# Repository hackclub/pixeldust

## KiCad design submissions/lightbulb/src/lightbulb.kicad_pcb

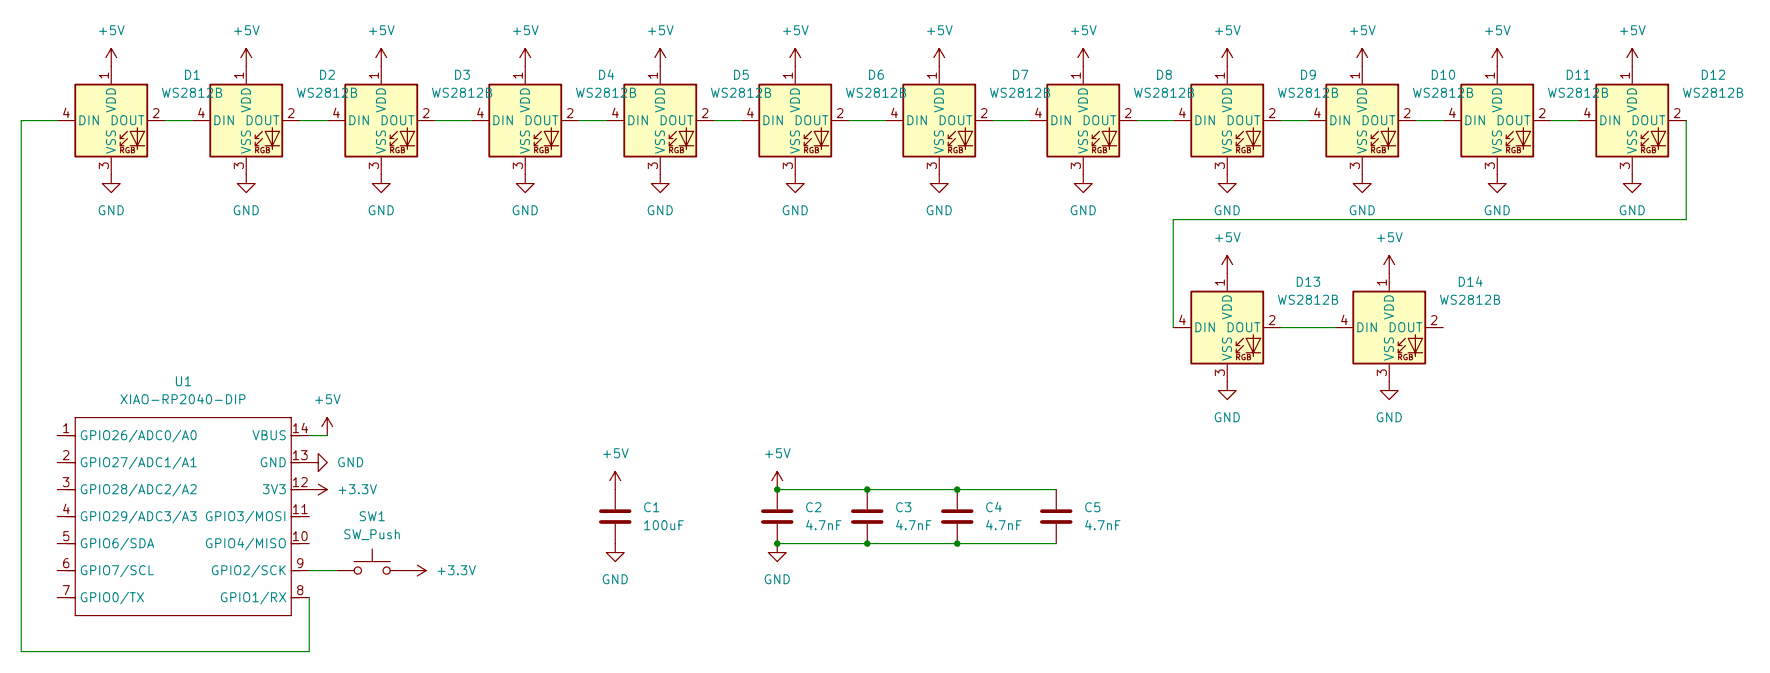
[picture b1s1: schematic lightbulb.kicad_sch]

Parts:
C1: 100uF; C_1206_3216Metric_Pad1.33x1.80mm_HandSolder
C2, C3, C4, C5: 4.7nF; C_0402_1005Metric_Pad0.74x0.62mm_HandSolder
D1, D2, D3, D4, D5, D6, D7, D8, D9, D10, D11, D12, D13, D14: WS2812B; LED_WS2812B_PLCC4_5.0x5.0mm_P3.2mm
SW1: SW_Push; SW_Cherry_MX_1.00u_PCB
U1: XIAO-RP2040-DIP

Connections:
+3.3V: SW1.2, U1.12 (3V3)
+5V: C1.1, C2.1, C3.1, C4.1, C5.1, D1.1 (VDD), D2.1 (VDD), D3.1 (VDD), D4.1 (VDD), D5.1 (VDD), D6.1 (VDD), D7.1 (VDD), D8.1 (VDD), D9.1 (VDD), D10.1 (VDD), D11.1 (VDD), D12.1 (VDD), D13.1 (VDD), D14.1 (VDD), U1.14 (VBUS)
GND: C1.2, C2.2, C3.2, C4.2, C5.2, D1.3 (VSS), D2.3 (VSS), D3.3 (VSS), D4.3 (VSS), D5.3 (VSS), D6.3 (VSS), D7.3 (VSS), D8.3 (VSS), D9.3 (VSS), D10.3 (VSS), D11.3 (VSS), D12.3 (VSS), D13.3 (VSS), D14.3 (VSS), U1.13 (GND)
unnamed: D1.4 (DIN), U1.8 (GPIO1/RX)
unnamed: D1.2 (DOUT), D2.4 (DIN)
unnamed: D2.2 (DOUT), D3.4 (DIN)
unnamed: D3.2 (DOUT), D4.4 (DIN)
unnamed: D4.2 (DOUT), D5.4 (DIN)
unnamed: D5.2 (DOUT), D6.4 (DIN)
unnamed: D6.2 (DOUT), D7.4 (DIN)
unnamed: D7.2 (DOUT), D8.4 (DIN)
unnamed: D8.2 (DOUT), D9.4 (DIN)
unnamed: D9.2 (DOUT), D10.4 (DIN)
unnamed: D10.2 (DOUT), D11.4 (DIN)
unnamed: D11.2 (DOUT), D12.4 (DIN)
unnamed: D12.2 (DOUT), D13.4 (DIN)
unnamed: D13.2 (DOUT), D14.4 (DIN)
unnamed: SW1.1, U1.9 (GPIO2/SCK)

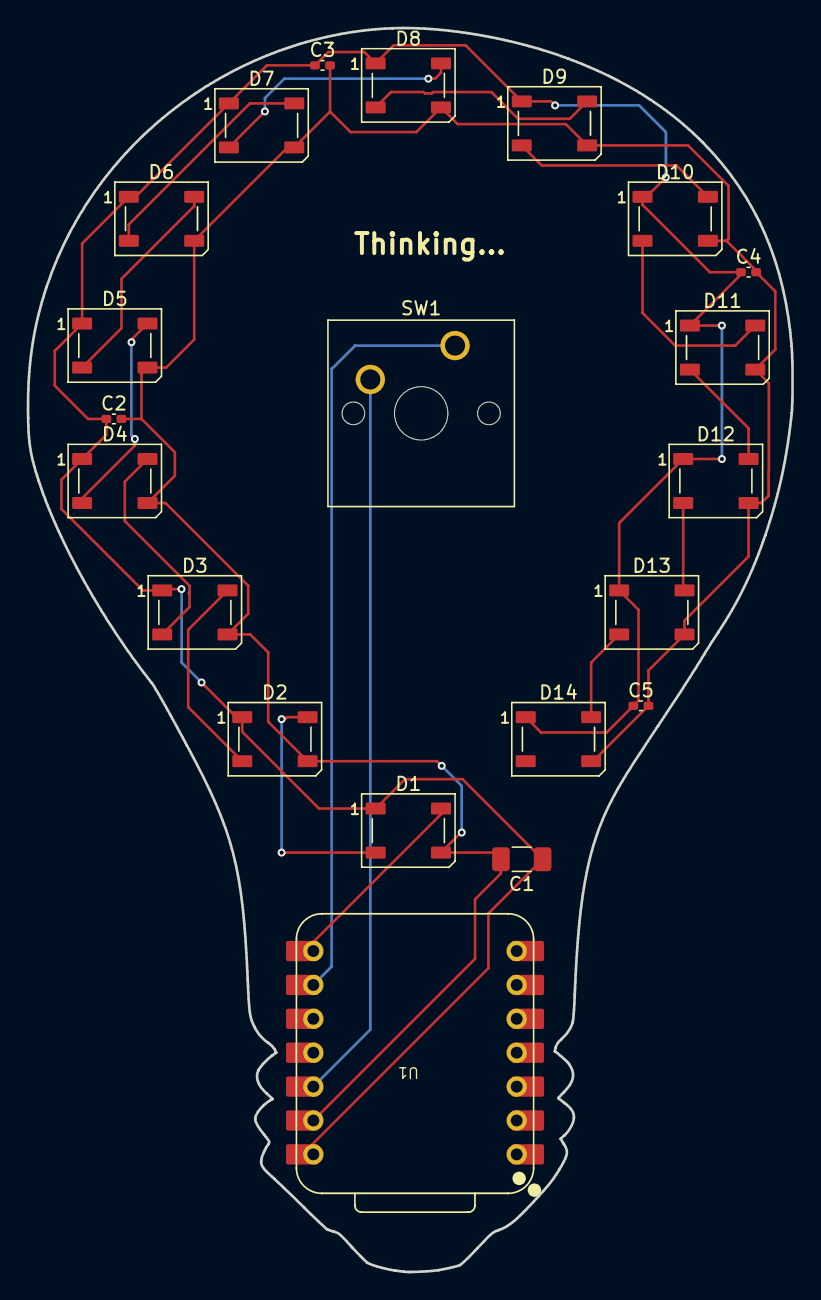
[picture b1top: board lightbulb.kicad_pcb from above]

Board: 2 copper layers, 57.3 x 93.2 mm, 21 parts (0 on the bottom side), 18 nets.

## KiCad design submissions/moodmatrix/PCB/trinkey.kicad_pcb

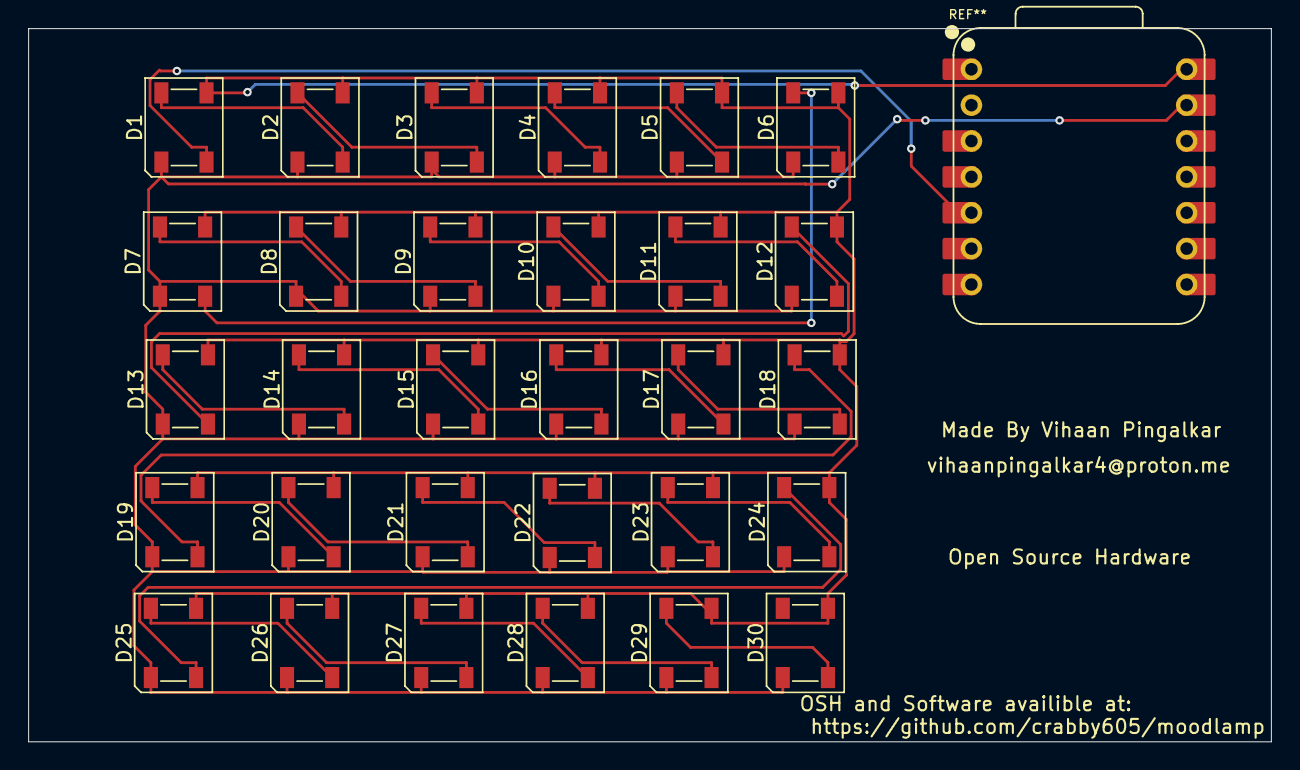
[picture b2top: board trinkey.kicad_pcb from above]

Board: 2 copper layers, 88.0 x 50.5 mm, 30 parts (0 on the bottom side), 31 nets.

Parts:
D1, D2, D3, D4, D5, D6, D7, D8, D9, D10, D11, D12, D13, D14, D15, D16, D17, D18, D19, D20, D21, D22, D23, D24, D25, D26, D27, D28, D29, D30: SK6812; LED_SK6812_PLCC4_5.0x5.0mm_P3.2mm

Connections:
+5V: D1.3 (VDD), D2.3 (VDD), D3.3 (VDD), D4.3 (VDD), D5.3 (VDD), D6.3 (VDD), D7.3 (VDD), D8.3 (VDD), D9.3 (VDD), D10.3 (VDD), D11.3 (VDD), D12.3 (VDD), D13.3 (VDD), D14.3 (VDD), D15.3 (VDD), D16.3 (VDD), D17.3 (VDD), D18.3 (VDD), D19.3 (VDD), D20.3 (VDD), D21.3 (VDD), D22.3 (VDD), D23.3 (VDD), D24.3 (VDD), D25.3 (VDD), D26.3 (VDD), D27.3 (VDD), D28.3 (VDD), D29.3 (VDD), D30.3 (VDD)
GND: D1.1 (VSS), D2.1 (VSS), D3.1 (VSS), D4.1 (VSS), D5.1 (VSS), D6.1 (VSS), D7.1 (VSS), D8.1 (VSS), D9.1 (VSS), D10.1 (VSS), D11.1 (VSS), D12.1 (VSS), D13.1 (VSS), D14.1 (VSS), D15.1 (VSS), D16.1 (VSS), D17.1 (VSS), D18.1 (VSS), D19.1 (VSS), D20.1 (VSS), D21.1 (VSS), D22.1 (VSS), D23.1 (VSS), D24.1 (VSS), D25.1 (VSS), D26.1 (VSS), D27.1 (VSS), D28.1 (VSS), D29.1 (VSS), D30.1 (VSS)
unnamed: D1.4 (DOUT), D2.2 (DIN)
unnamed: D2.4 (DOUT), D3.2 (DIN)
unnamed: D3.4 (DOUT), D4.2 (DIN)
unnamed: D4.4 (DOUT), D5.2 (DIN)
unnamed: D5.4 (DOUT), D6.2 (DIN)
unnamed: D6.4 (DOUT), D7.2 (DIN)
unnamed: D7.4 (DOUT), D8.2 (DIN)
unnamed: D8.4 (DOUT), D9.2 (DIN)
unnamed: D9.4 (DOUT), D10.2 (DIN)
unnamed: D10.4 (DOUT), D11.2 (DIN)
unnamed: D11.4 (DOUT), D12.2 (DIN)
unnamed: D12.4 (DOUT), D13.2 (DIN)
unnamed: D13.4 (DOUT), D14.2 (DIN)
unnamed: D14.4 (DOUT), D15.2 (DIN)
unnamed: D15.4 (DOUT), D16.2 (DIN)
unnamed: D16.4 (DOUT), D17.2 (DIN)
unnamed: D17.4 (DOUT), D18.2 (DIN)
unnamed: D18.4 (DOUT), D19.2 (DIN)
unnamed: D19.4 (DOUT), D20.2 (DIN)
unnamed: D20.4 (DOUT), D21.2 (DIN)
unnamed: D21.4 (DOUT), D22.2 (DIN)
unnamed: D22.4 (DOUT), D23.2 (DIN)
unnamed: D23.4 (DOUT), D24.2 (DIN)
unnamed: D24.4 (DOUT), D25.2 (DIN)
unnamed: D25.4 (DOUT), D26.2 (DIN)
unnamed: D26.4 (DOUT), D27.2 (DIN)
unnamed: D27.4 (DOUT), D28.2 (DIN)
unnamed: D28.4 (DOUT), D29.2 (DIN)
unnamed: D29.4 (DOUT), D30.2 (DIN)

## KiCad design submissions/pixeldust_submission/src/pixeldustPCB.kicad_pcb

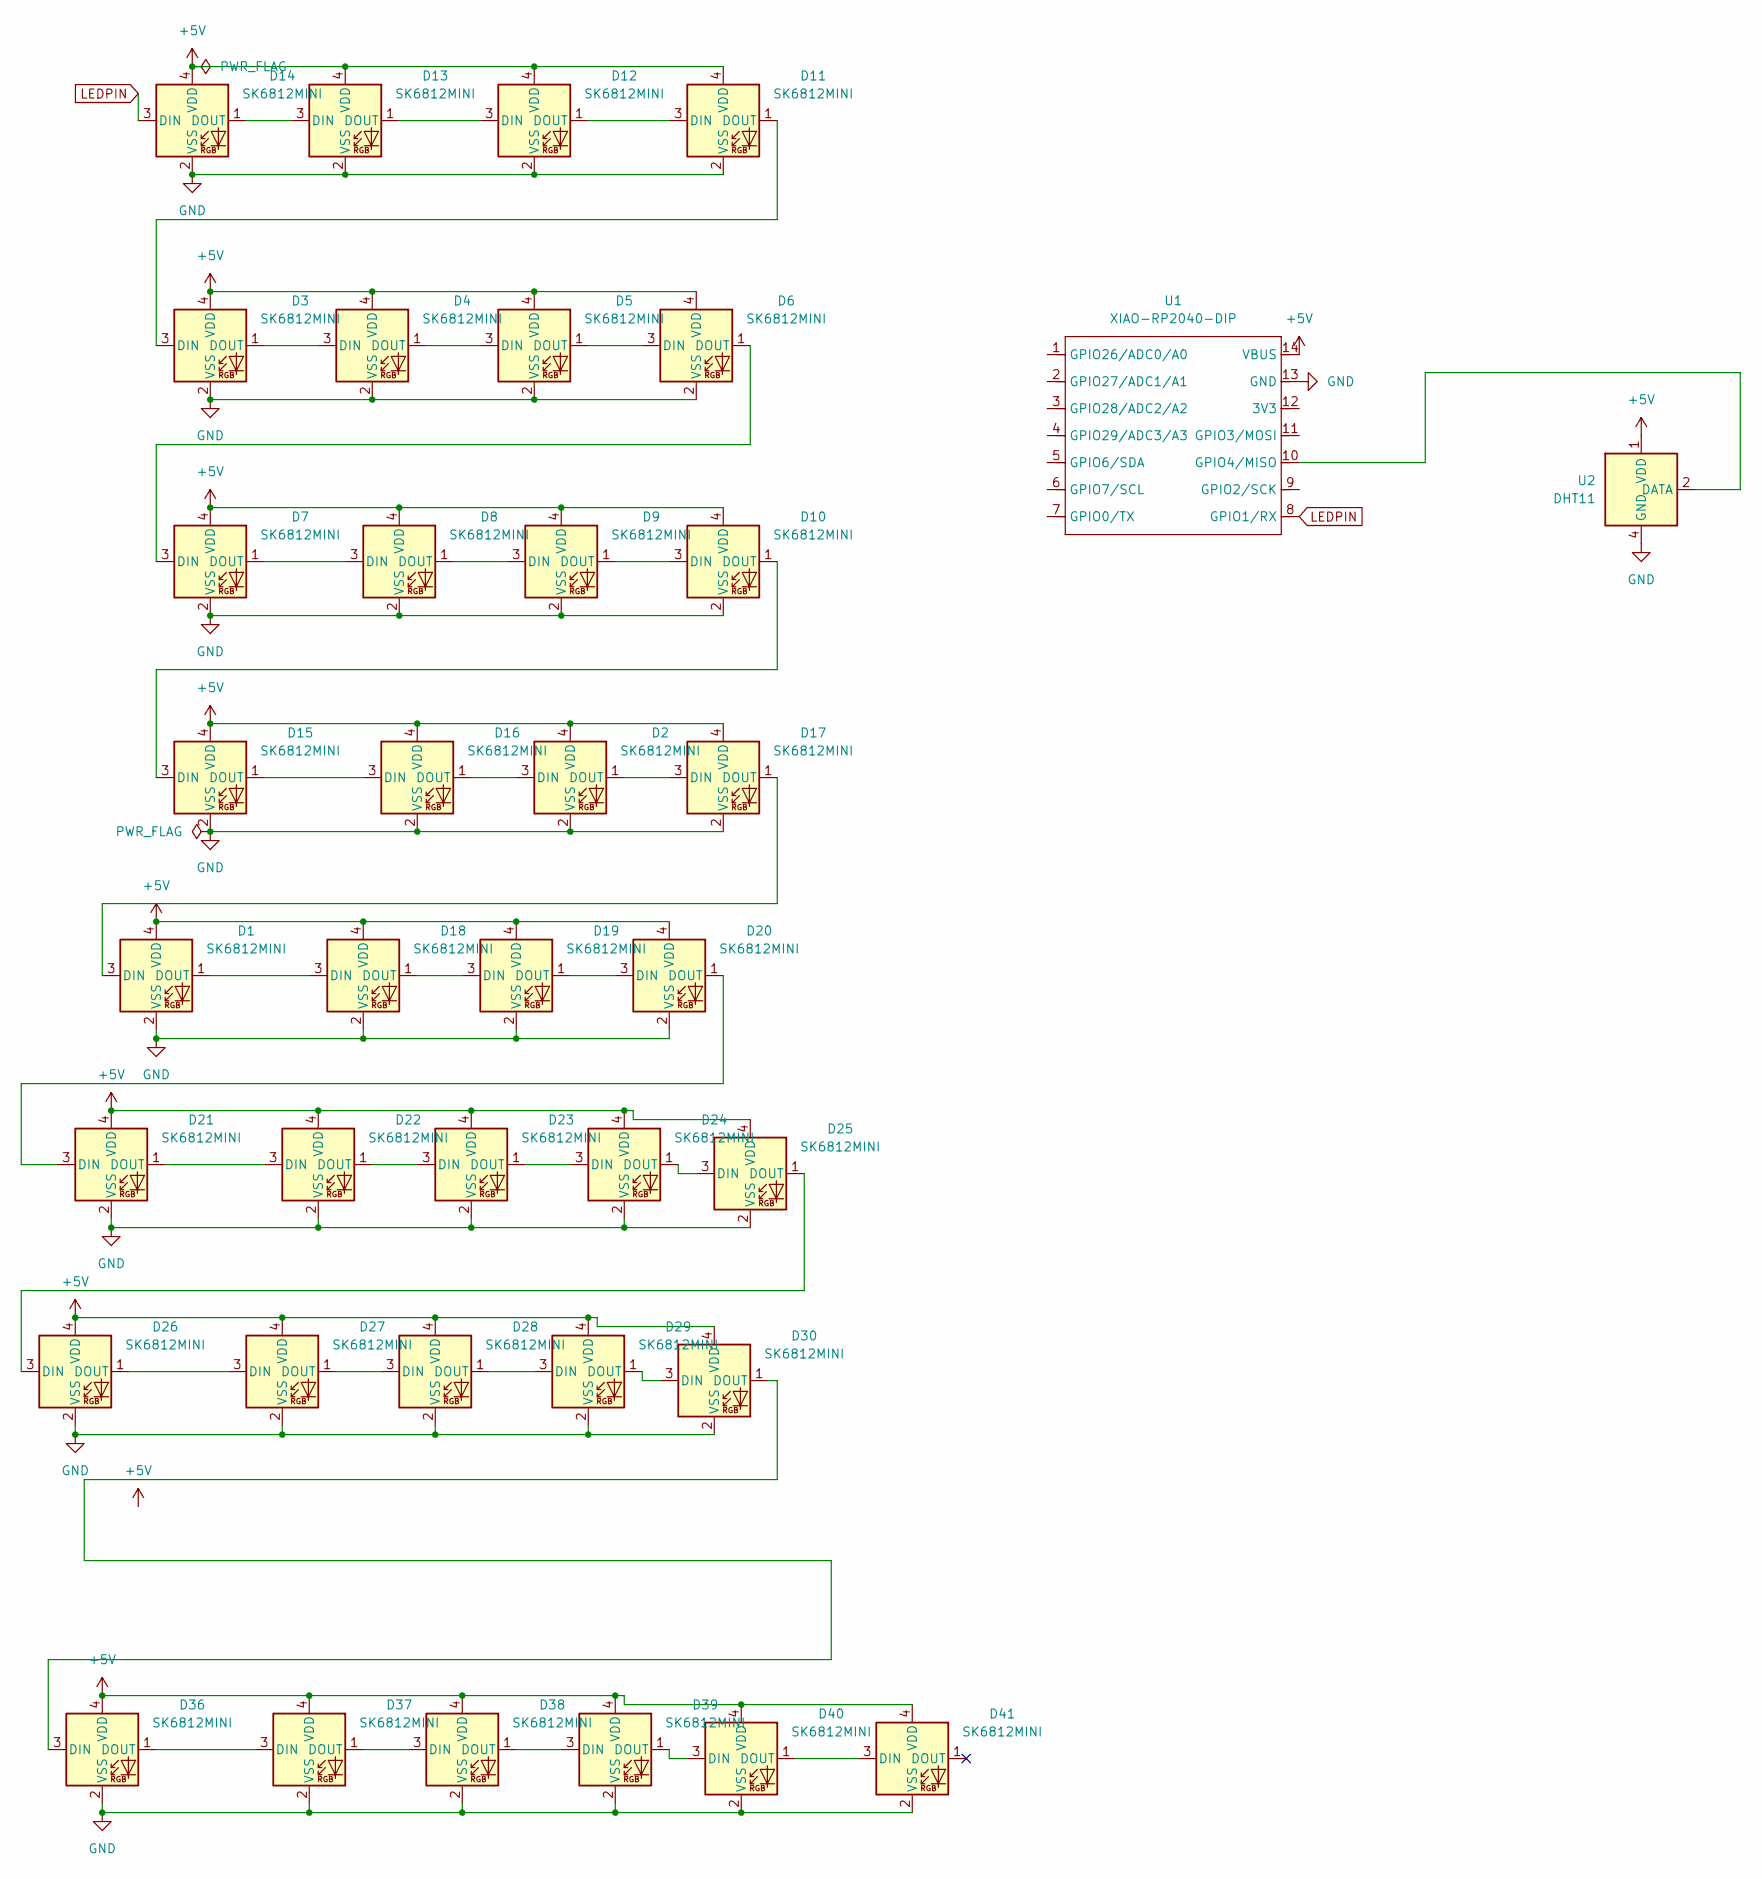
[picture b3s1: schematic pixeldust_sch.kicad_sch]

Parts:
D1, D2, D3, D4, D5, D6, D7, D8, D9, D10, D11, D12, D13, D14, D15, D16, D17, D18, D19, D20, D21, D22, D23, D24, D25, D26, D27, D28, D29, D30, D36, D37, D38, D39, D40, D41: SK6812MINI; LED_WS2812B_PLCC4_5.0x5.0mm_P3.2mm
U1: XIAO-RP2040-DIP
U2: DHT11; Aosong_DHT11_5.5x12.0_P2.54mm

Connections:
+5V: D1.4 (VDD), D2.4 (VDD), D3.4 (VDD), D4.4 (VDD), D5.4 (VDD), D6.4 (VDD), D7.4 (VDD), D8.4 (VDD), D9.4 (VDD), D10.4 (VDD), D11.4 (VDD), D12.4 (VDD), D13.4 (VDD), D14.4 (VDD), D15.4 (VDD), D16.4 (VDD), D17.4 (VDD), D18.4 (VDD), D19.4 (VDD), D20.4 (VDD), D21.4 (VDD), D22.4 (VDD), D23.4 (VDD), D24.4 (VDD), D25.4 (VDD), D26.4 (VDD), D27.4 (VDD), D28.4 (VDD), D29.4 (VDD), D30.4 (VDD), D36.4 (VDD), D37.4 (VDD), D38.4 (VDD), D39.4 (VDD), D40.4 (VDD), D41.4 (VDD), U1.14 (VBUS), U2.1 (VDD)
GND: D1.2 (VSS), D2.2 (VSS), D3.2 (VSS), D4.2 (VSS), D5.2 (VSS), D6.2 (VSS), D7.2 (VSS), D8.2 (VSS), D9.2 (VSS), D10.2 (VSS), D11.2 (VSS), D12.2 (VSS), D13.2 (VSS), D14.2 (VSS), D15.2 (VSS), D16.2 (VSS), D17.2 (VSS), D18.2 (VSS), D19.2 (VSS), D20.2 (VSS), D21.2 (VSS), D22.2 (VSS), D23.2 (VSS), D24.2 (VSS), D25.2 (VSS), D26.2 (VSS), D27.2 (VSS), D28.2 (VSS), D29.2 (VSS), D30.2 (VSS), D36.2 (VSS), D37.2 (VSS), D38.2 (VSS), D39.2 (VSS), D40.2 (VSS), D41.2 (VSS), U1.13 (GND), U2.4 (GND)
LEDPIN: D14.3 (DIN), U1.8 (GPIO1/RX)
unnamed: D1.3 (DIN), D17.1 (DOUT)
unnamed: D1.1 (DOUT), D18.3 (DIN)
unnamed: D3.1 (DOUT), D4.3 (DIN)
unnamed: D4.1 (DOUT), D5.3 (DIN)
unnamed: D5.1 (DOUT), D6.3 (DIN)
unnamed: D6.1 (DOUT), D7.3 (DIN)
unnamed: D7.1 (DOUT), D8.3 (DIN)
unnamed: D8.1 (DOUT), D9.3 (DIN)
unnamed: D9.1 (DOUT), D10.3 (DIN)
unnamed: D10.1 (DOUT), D15.3 (DIN)
unnamed: D11.3 (DIN), D12.1 (DOUT)
unnamed: D3.3 (DIN), D11.1 (DOUT)
unnamed: D12.3 (DIN), D13.1 (DOUT)
unnamed: D13.3 (DIN), D14.1 (DOUT)
unnamed: D15.1 (DOUT), D16.3 (DIN)
unnamed: D2.3 (DIN), D16.1 (DOUT)
unnamed: D2.1 (DOUT), D17.3 (DIN)
unnamed: D18.1 (DOUT), D19.3 (DIN)
unnamed: D19.1 (DOUT), D20.3 (DIN)
unnamed: D20.1 (DOUT), D21.3 (DIN)
unnamed: D21.1 (DOUT), D22.3 (DIN)
unnamed: D22.1 (DOUT), D23.3 (DIN)
unnamed: D23.1 (DOUT), D24.3 (DIN)
unnamed: D24.1 (DOUT), D25.3 (DIN)
unnamed: D25.1 (DOUT), D26.3 (DIN)
unnamed: D26.1 (DOUT), D27.3 (DIN)
unnamed: D27.1 (DOUT), D28.3 (DIN)
unnamed: D28.1 (DOUT), D29.3 (DIN)
unnamed: D29.1 (DOUT), D30.3 (DIN)
unnamed: D30.1 (DOUT), D36.3 (DIN)
unnamed: D36.1 (DOUT), D37.3 (DIN)
unnamed: D37.1 (DOUT), D38.3 (DIN)
unnamed: D38.1 (DOUT), D39.3 (DIN)
unnamed: D39.1 (DOUT), D40.3 (DIN)
unnamed: D40.1 (DOUT), D41.3 (DIN)
unnamed: U1.10 (GPIO4/MISO), U2.2 (DATA)

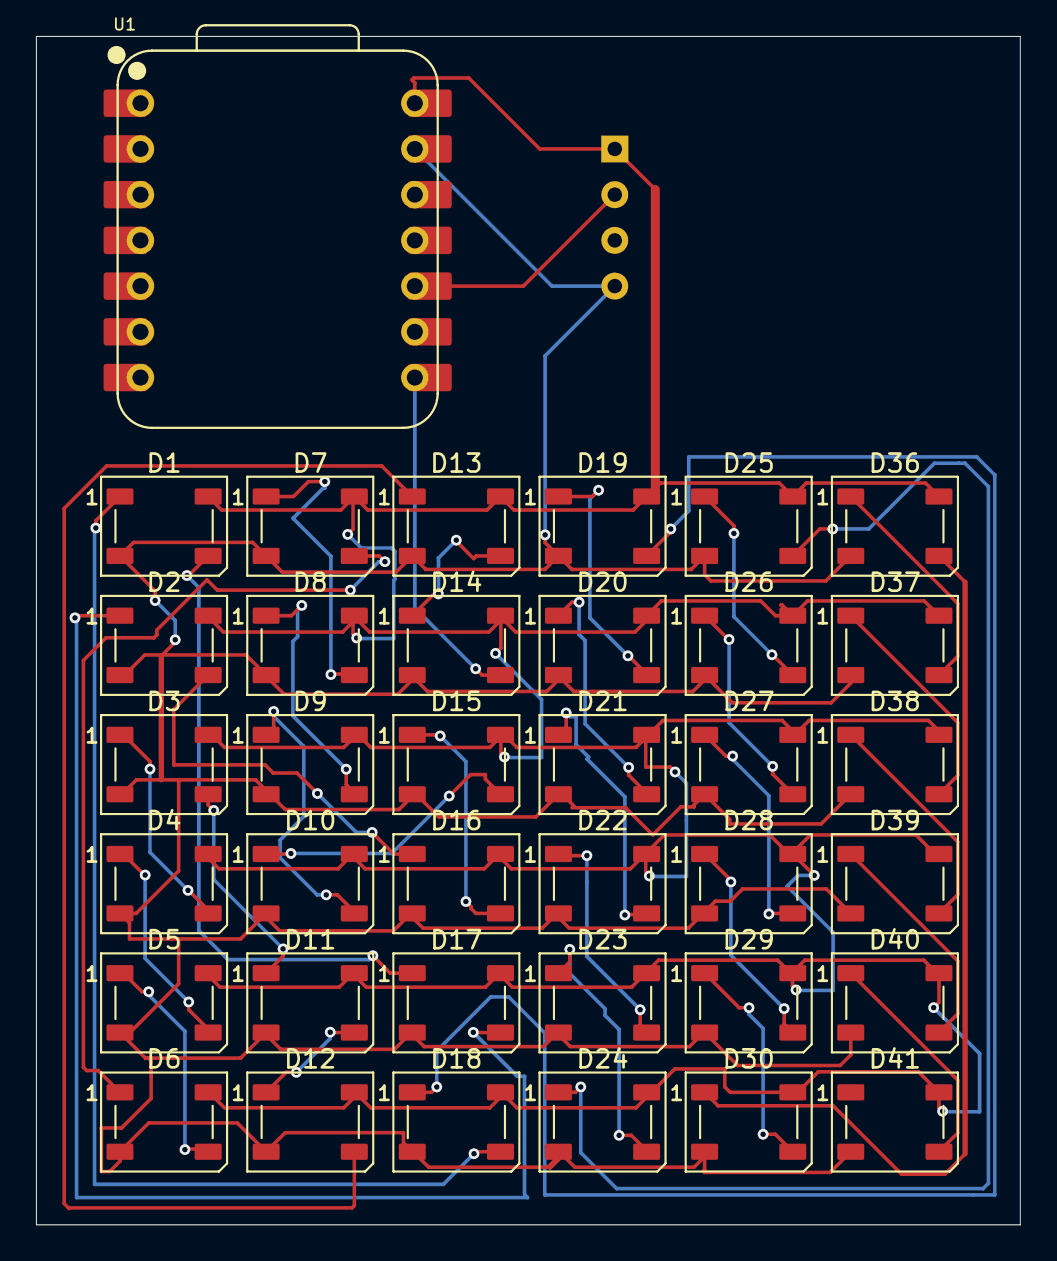
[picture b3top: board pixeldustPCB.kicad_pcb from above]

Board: 2 copper layers, 54.7 x 66.0 mm, 38 parts (1 on the bottom side), 39 nets.

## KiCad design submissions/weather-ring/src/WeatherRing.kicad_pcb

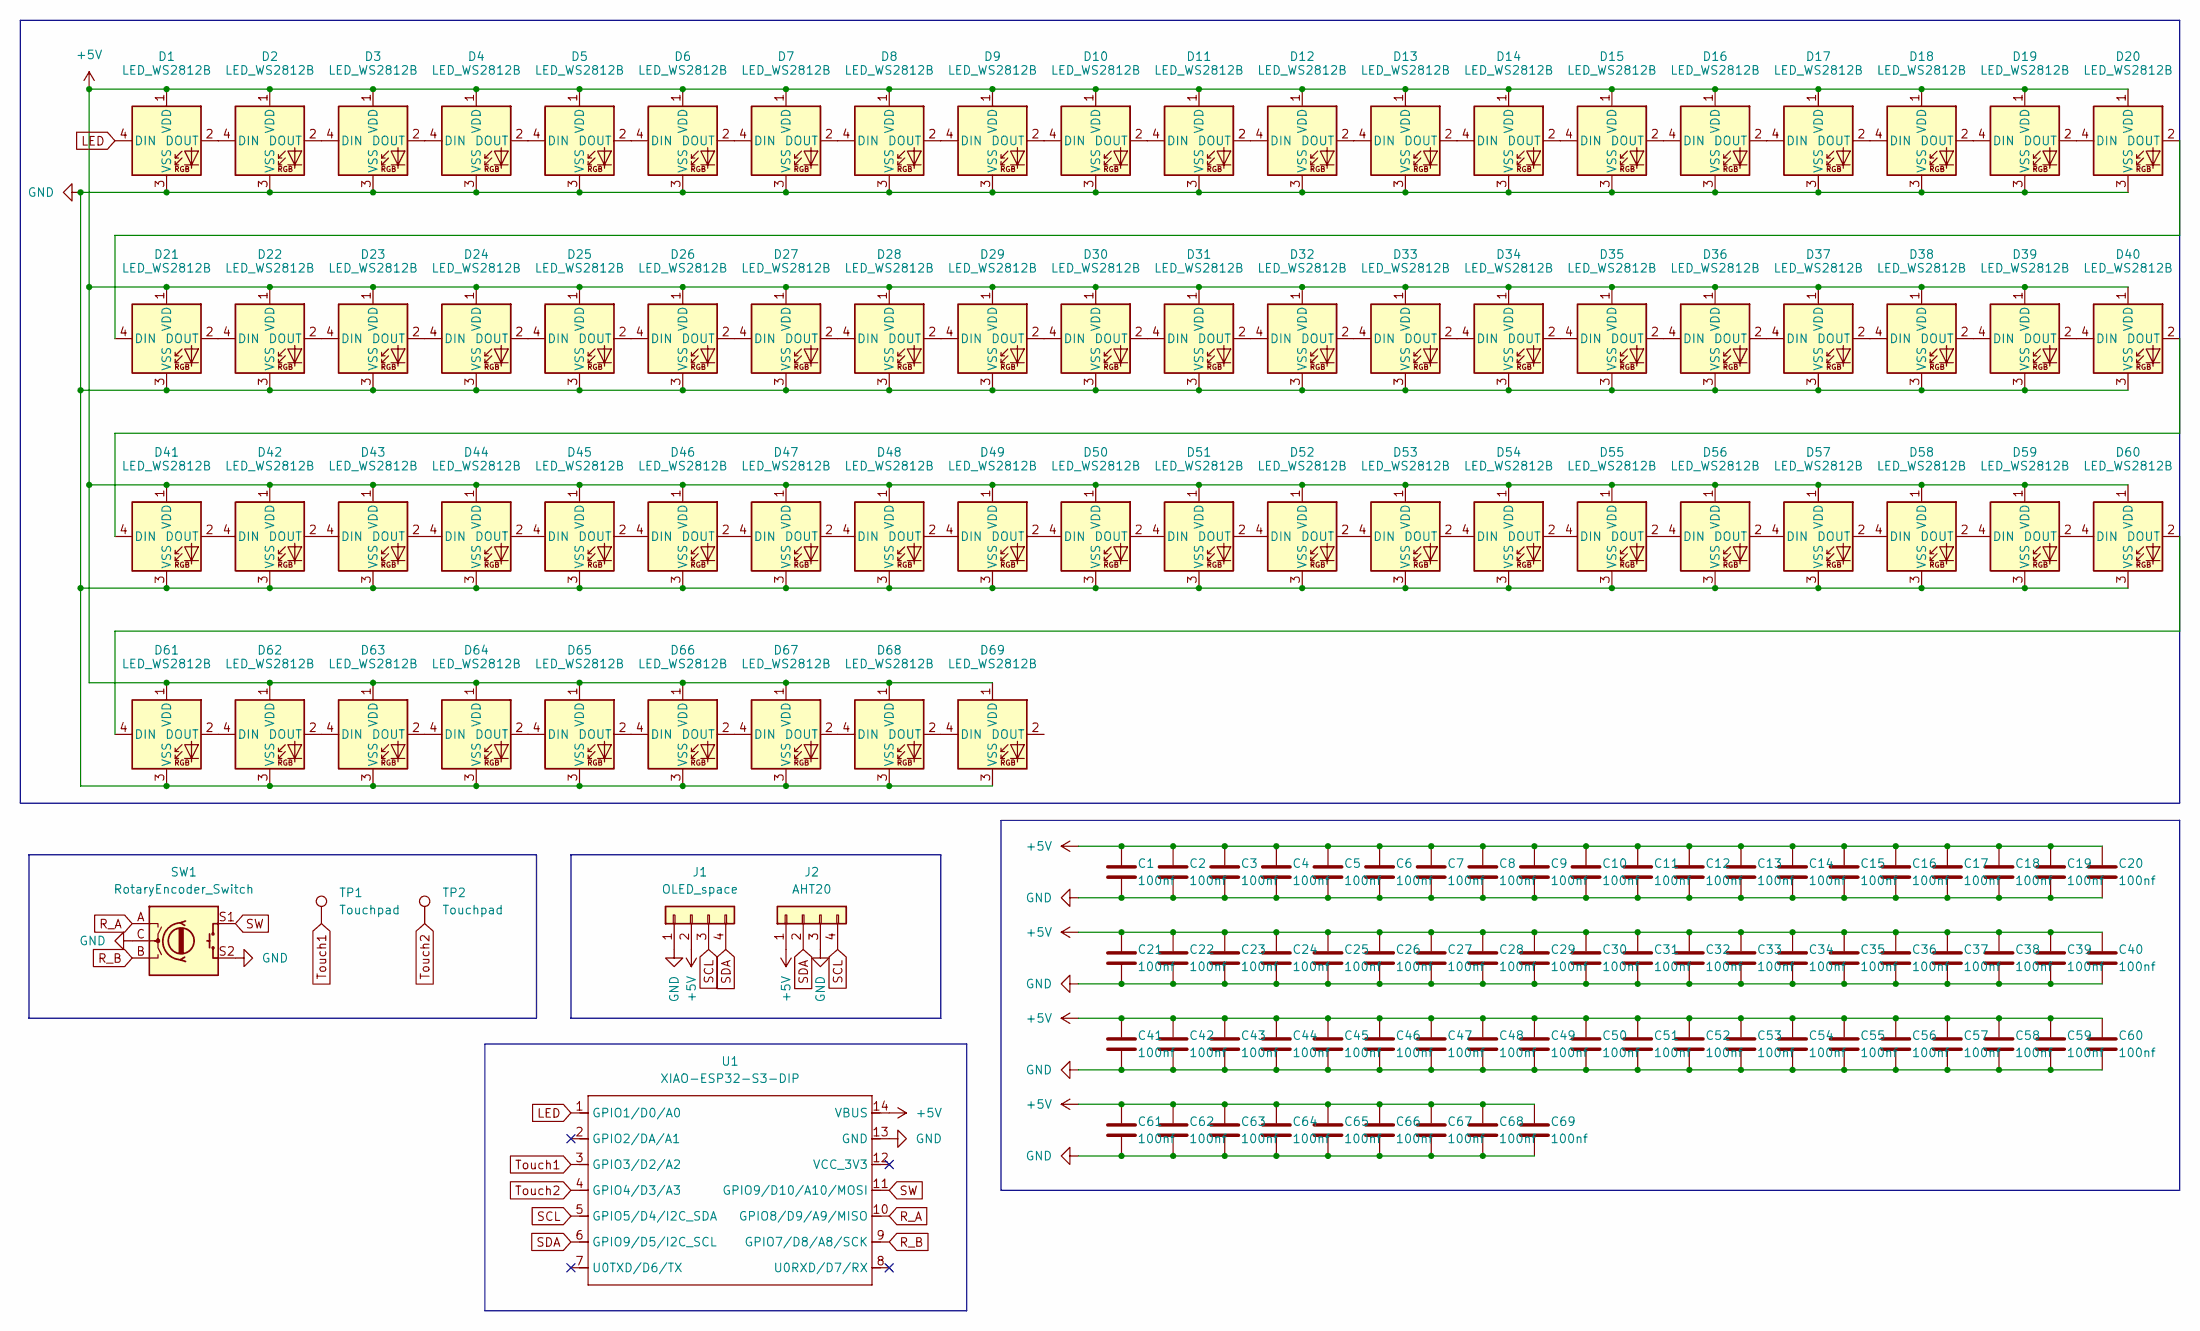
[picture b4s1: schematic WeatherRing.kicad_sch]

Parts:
C1, C2, C3, C4, C5, C6, C7, C8, C9, C10, C11, C12, C13, C14, C15, C16, C17, C18, C19, C20, C21, C22, C23, C24, C25, C26, C27, C28, C29, C30, C31, C32, C33, C34, C35, C36, C37, C38, C39, C40, C41, C42, C43, C44, C45, C46, C47, C48, C49, C50, C51, C52, C53, C54, C55, C56, C57, C58, C59, C60, C61, C62, C63, C64, C65, C66, C67, C68, C69: 100nf; C_0805_2012Metric_HandSolder_EDITED
D1, D2, D3, D4, D5, D6, D7, D8, D9, D10, D11, D12, D13, D14, D15, D16, D17, D18, D19, D20, D21, D22, D23, D24, D25, D26, D27, D28, D29, D30, D31, D32, D33, D34, D35, D36, D37, D38, D39, D40, D41, D42, D43, D44, D45, D46, D47, D48, D49, D50, D51, D52, D53, D54, D55, D56, D57, D58, D59, D60, D61, D62, D63, D64, D65, D66, D67, D68, D69: LED_WS2812B; LED_WS2812B_EDITED
J1: OLED_space; PinHeader_1x04_P2.54mm_Vertical
J2: AHT20; PinHeader_1x04_P2.54mm_Vertical
SW1: RotaryEncoder_Switch; RotaryEncoder_EC11
TP1, TP2: Touchpad; TestPoint_Pad_D10.0mm
U1: XIAO-ESP32-S3-DIP; XIAO-ESP32S3-DIP

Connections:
+5V: C1.1, C2.1, C3.1, C4.1, C5.1, C6.1, C7.1, C8.1, C9.1, C10.1, C11.1, C12.1, C13.1, C14.1, C15.1, C16.1, C17.1, C18.1, C19.1, C20.1, C21.1, C22.1, C23.1, C24.1, C25.1, C26.1, C27.1, C28.1, C29.1, C30.1, C31.1, C32.1, C33.1, C34.1, C35.1, C36.1, C37.1, C38.1, C39.1, C40.1, C41.1, C42.1, C43.1, C44.1, C45.1, C46.1, C47.1, C48.1, C49.1, C50.1, C51.1, C52.1, C53.1, C54.1, C55.1, C56.1, C57.1, C58.1, C59.1, C60.1, C61.1, C62.1, C63.1, C64.1, C65.1, C66.1, C67.1, C68.1, C69.1, D1.1 (VDD), D2.1 (VDD), D3.1 (VDD), D4.1 (VDD), D5.1 (VDD), D6.1 (VDD), D7.1 (VDD), D8.1 (VDD), D9.1 (VDD), D10.1 (VDD), D11.1 (VDD), D12.1 (VDD), D13.1 (VDD), D14.1 (VDD), D15.1 (VDD), D16.1 (VDD), D17.1 (VDD), D18.1 (VDD), D19.1 (VDD), D20.1 (VDD), D21.1 (VDD), D22.1 (VDD), D23.1 (VDD), D24.1 (VDD), D25.1 (VDD), D26.1 (VDD), D27.1 (VDD), D28.1 (VDD), D29.1 (VDD), D30.1 (VDD), D31.1 (VDD), D32.1 (VDD), D33.1 (VDD), D34.1 (VDD), D35.1 (VDD), D36.1 (VDD), D37.1 (VDD), D38.1 (VDD), D39.1 (VDD), D40.1 (VDD), D41.1 (VDD), D42.1 (VDD), D43.1 (VDD), D44.1 (VDD), D45.1 (VDD), D46.1 (VDD), D47.1 (VDD), D48.1 (VDD), D49.1 (VDD), D50.1 (VDD), D51.1 (VDD), D52.1 (VDD), D53.1 (VDD), D54.1 (VDD), D55.1 (VDD), D56.1 (VDD), D57.1 (VDD), D58.1 (VDD), D59.1 (VDD), D60.1 (VDD), D61.1 (VDD), D62.1 (VDD), D63.1 (VDD), D64.1 (VDD), D65.1 (VDD), D66.1 (VDD), D67.1 (VDD), D68.1 (VDD), D69.1 (VDD), J1.2, J2.1, U1.14 (VBUS)
GND: C1.2, C2.2, C3.2, C4.2, C5.2, C6.2, C7.2, C8.2, C9.2, C10.2, C11.2, C12.2, C13.2, C14.2, C15.2, C16.2, C17.2, C18.2, C19.2, C20.2, C21.2, C22.2, C23.2, C24.2, C25.2, C26.2, C27.2, C28.2, C29.2, C30.2, C31.2, C32.2, C33.2, C34.2, C35.2, C36.2, C37.2, C38.2, C39.2, C40.2, C41.2, C42.2, C43.2, C44.2, C45.2, C46.2, C47.2, C48.2, C49.2, C50.2, C51.2, C52.2, C53.2, C54.2, C55.2, C56.2, C57.2, C58.2, C59.2, C60.2, C61.2, C62.2, C63.2, C64.2, C65.2, C66.2, C67.2, C68.2, C69.2, D1.3 (VSS), D2.3 (VSS), D3.3 (VSS), D4.3 (VSS), D5.3 (VSS), D6.3 (VSS), D7.3 (VSS), D8.3 (VSS), D9.3 (VSS), D10.3 (VSS), D11.3 (VSS), D12.3 (VSS), D13.3 (VSS), D14.3 (VSS), D15.3 (VSS), D16.3 (VSS), D17.3 (VSS), D18.3 (VSS), D19.3 (VSS), D20.3 (VSS), D21.3 (VSS), D22.3 (VSS), D23.3 (VSS), D24.3 (VSS), D25.3 (VSS), D26.3 (VSS), D27.3 (VSS), D28.3 (VSS), D29.3 (VSS), D30.3 (VSS), D31.3 (VSS), D32.3 (VSS), D33.3 (VSS), D34.3 (VSS), D35.3 (VSS), D36.3 (VSS), D37.3 (VSS), D38.3 (VSS), D39.3 (VSS), D40.3 (VSS), D41.3 (VSS), D42.3 (VSS), D43.3 (VSS), D44.3 (VSS), D45.3 (VSS), D46.3 (VSS), D47.3 (VSS), D48.3 (VSS), D49.3 (VSS), D50.3 (VSS), D51.3 (VSS), D52.3 (VSS), D53.3 (VSS), D54.3 (VSS), D55.3 (VSS), D56.3 (VSS), D57.3 (VSS), D58.3 (VSS), D59.3 (VSS), D60.3 (VSS), D61.3 (VSS), D62.3 (VSS), D63.3 (VSS), D64.3 (VSS), D65.3 (VSS), D66.3 (VSS), D67.3 (VSS), D68.3 (VSS), D69.3 (VSS), J1.1, J2.3, SW1.C, SW1.S2, U1.13 (GND)
LED: D1.4 (DIN), U1.1 (GPIO1/D0/A0)
unnamed: D1.2 (DOUT), D2.4 (DIN)
unnamed: D2.2 (DOUT), D3.4 (DIN)
unnamed: D3.2 (DOUT), D4.4 (DIN)
unnamed: D4.2 (DOUT), D5.4 (DIN)
unnamed: D5.2 (DOUT), D6.4 (DIN)
unnamed: D6.2 (DOUT), D7.4 (DIN)
unnamed: D7.2 (DOUT), D8.4 (DIN)
unnamed: D8.2 (DOUT), D9.4 (DIN)
unnamed: D9.2 (DOUT), D10.4 (DIN)
unnamed: D10.2 (DOUT), D11.4 (DIN)
unnamed: D11.2 (DOUT), D12.4 (DIN)
unnamed: D12.2 (DOUT), D13.4 (DIN)
unnamed: D13.2 (DOUT), D14.4 (DIN)
unnamed: D14.2 (DOUT), D15.4 (DIN)
unnamed: D15.2 (DOUT), D16.4 (DIN)
unnamed: D16.2 (DOUT), D17.4 (DIN)
unnamed: D17.2 (DOUT), D18.4 (DIN)
unnamed: D18.2 (DOUT), D19.4 (DIN)
unnamed: D19.2 (DOUT), D20.4 (DIN)
unnamed: D20.2 (DOUT), D21.4 (DIN)
unnamed: D21.2 (DOUT), D22.4 (DIN)
unnamed: D22.2 (DOUT), D23.4 (DIN)
unnamed: D23.2 (DOUT), D24.4 (DIN)
unnamed: D24.2 (DOUT), D25.4 (DIN)
unnamed: D25.2 (DOUT), D26.4 (DIN)
unnamed: D26.2 (DOUT), D27.4 (DIN)
unnamed: D27.2 (DOUT), D28.4 (DIN)
unnamed: D28.2 (DOUT), D29.4 (DIN)
unnamed: D29.2 (DOUT), D30.4 (DIN)
unnamed: D30.2 (DOUT), D31.4 (DIN)
unnamed: D31.2 (DOUT), D32.4 (DIN)
unnamed: D32.2 (DOUT), D33.4 (DIN)
unnamed: D33.2 (DOUT), D34.4 (DIN)
unnamed: D34.2 (DOUT), D35.4 (DIN)
unnamed: D35.2 (DOUT), D36.4 (DIN)
unnamed: D36.2 (DOUT), D37.4 (DIN)
unnamed: D37.2 (DOUT), D38.4 (DIN)
unnamed: D38.2 (DOUT), D39.4 (DIN)
unnamed: D39.2 (DOUT), D40.4 (DIN)
unnamed: D40.2 (DOUT), D41.4 (DIN)
unnamed: D41.2 (DOUT), D42.4 (DIN)
unnamed: D42.2 (DOUT), D43.4 (DIN)
unnamed: D43.2 (DOUT), D44.4 (DIN)
unnamed: D44.2 (DOUT), D45.4 (DIN)
unnamed: D45.2 (DOUT), D46.4 (DIN)
unnamed: D46.2 (DOUT), D47.4 (DIN)
unnamed: D47.2 (DOUT), D48.4 (DIN)
unnamed: D48.2 (DOUT), D49.4 (DIN)
unnamed: D49.2 (DOUT), D50.4 (DIN)
unnamed: D50.2 (DOUT), D51.4 (DIN)
unnamed: D51.2 (DOUT), D52.4 (DIN)
unnamed: D52.2 (DOUT), D53.4 (DIN)
unnamed: D53.2 (DOUT), D54.4 (DIN)
unnamed: D54.2 (DOUT), D55.4 (DIN)
unnamed: D55.2 (DOUT), D56.4 (DIN)
unnamed: D56.2 (DOUT), D57.4 (DIN)
unnamed: D57.2 (DOUT), D58.4 (DIN)
unnamed: D58.2 (DOUT), D59.4 (DIN)
unnamed: D59.2 (DOUT), D60.4 (DIN)
unnamed: D60.2 (DOUT), D61.4 (DIN)
unnamed: D61.2 (DOUT), D62.4 (DIN)
unnamed: D62.2 (DOUT), D63.4 (DIN)
unnamed: D63.2 (DOUT), D64.4 (DIN)
unnamed: D64.2 (DOUT), D65.4 (DIN)
unnamed: D65.2 (DOUT), D66.4 (DIN)
unnamed: D66.2 (DOUT), D67.4 (DIN)
unnamed: D67.2 (DOUT), D68.4 (DIN)
unnamed: D68.2 (DOUT), D69.4 (DIN)
R_A: SW1.A, U1.10 (GPIO8/D9/A9/MISO)
R_B: SW1.B, U1.9 (GPIO7/D8/A8/SCK)
SCL: J1.3, J2.4, U1.5 (GPIO5/D4/I2C_SDA)
SDA: J1.4, J2.2, U1.6 (GPIO9/D5/I2C_SCL)
SW: SW1.S1, U1.11 (GPIO9/D10/A10/MOSI)
Touch1: TP1.1, U1.3 (GPIO3/D2/A2)
Touch2: TP2.1, U1.4 (GPIO4/D3/A3)

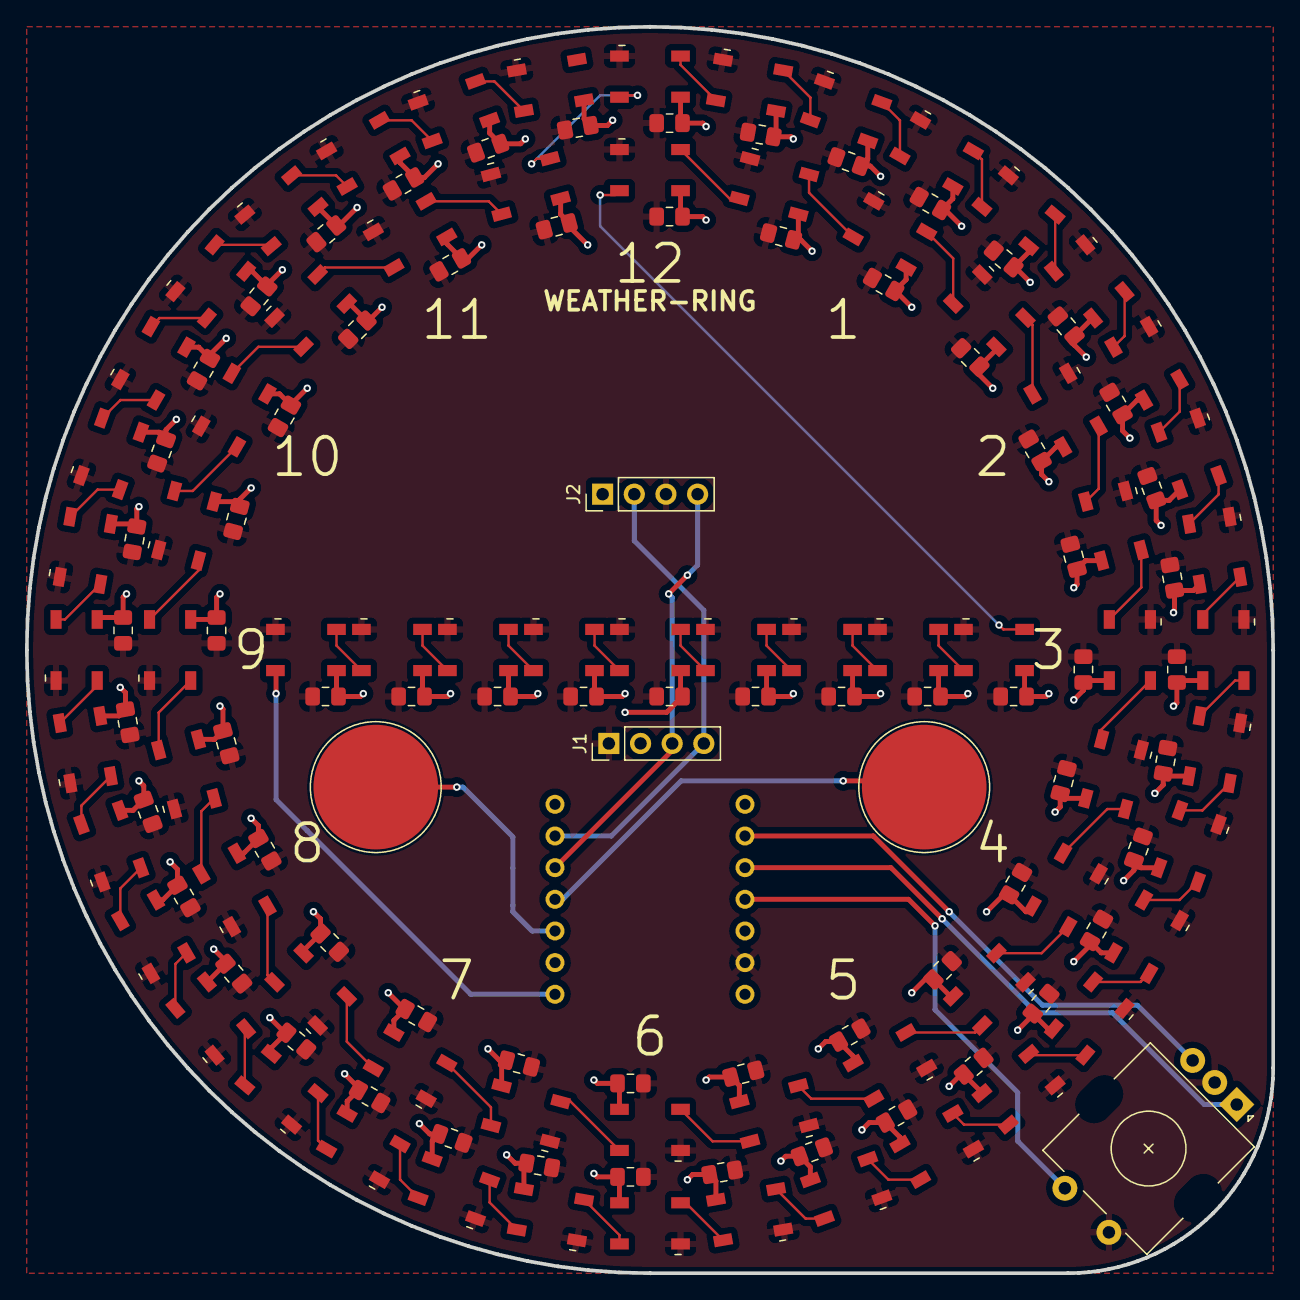
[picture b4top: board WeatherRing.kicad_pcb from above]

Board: 2 copper layers, 100.0 x 100.0 mm, 144 parts (1 on the bottom side), 78 nets.
